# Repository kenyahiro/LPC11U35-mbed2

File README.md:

# LPC11U35-mbed2

ローカルにmbed2のビルド環境を作成したものです。

ホストはDebian/testing, コンパイラはarm-none-eabi-gcc を使います。

ターゲットはLPC11U35のみ確認しています。

mbed-cliを使ってコンパイルできることを確認したあと, exportでMakefileを生成しました。

割り込みベクタにチェックサムを埋め込むため、 スタートアップとリンカスクリプトを修正しました。
また、CRPの値を設定しています。

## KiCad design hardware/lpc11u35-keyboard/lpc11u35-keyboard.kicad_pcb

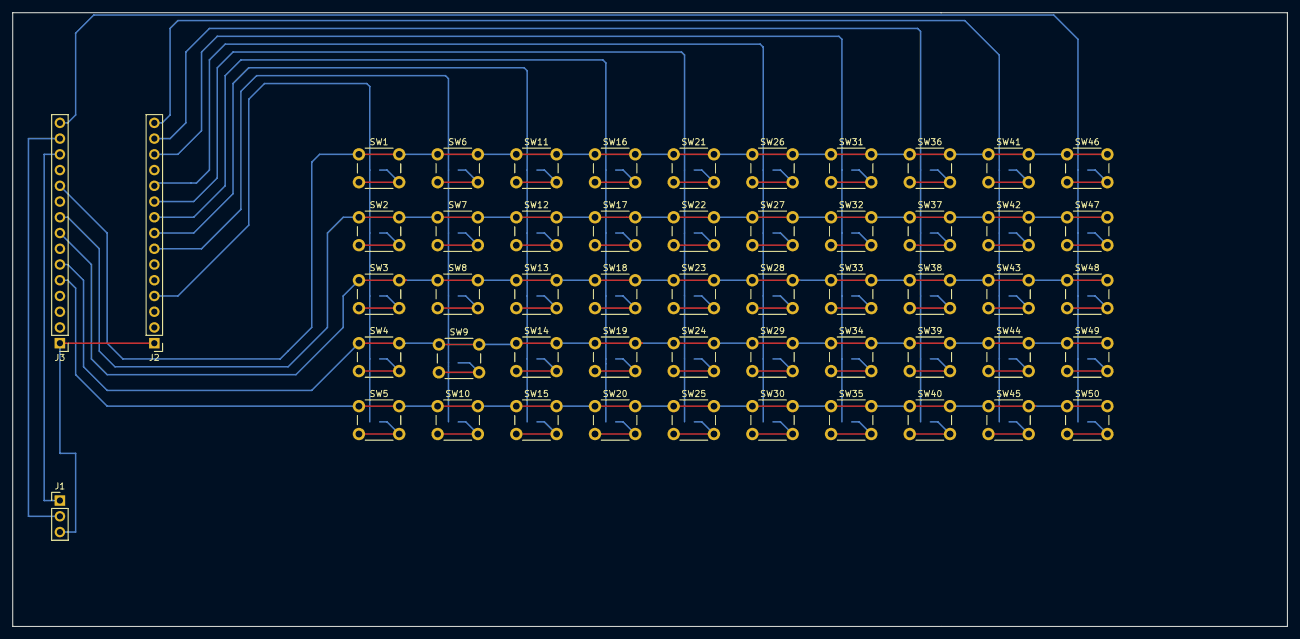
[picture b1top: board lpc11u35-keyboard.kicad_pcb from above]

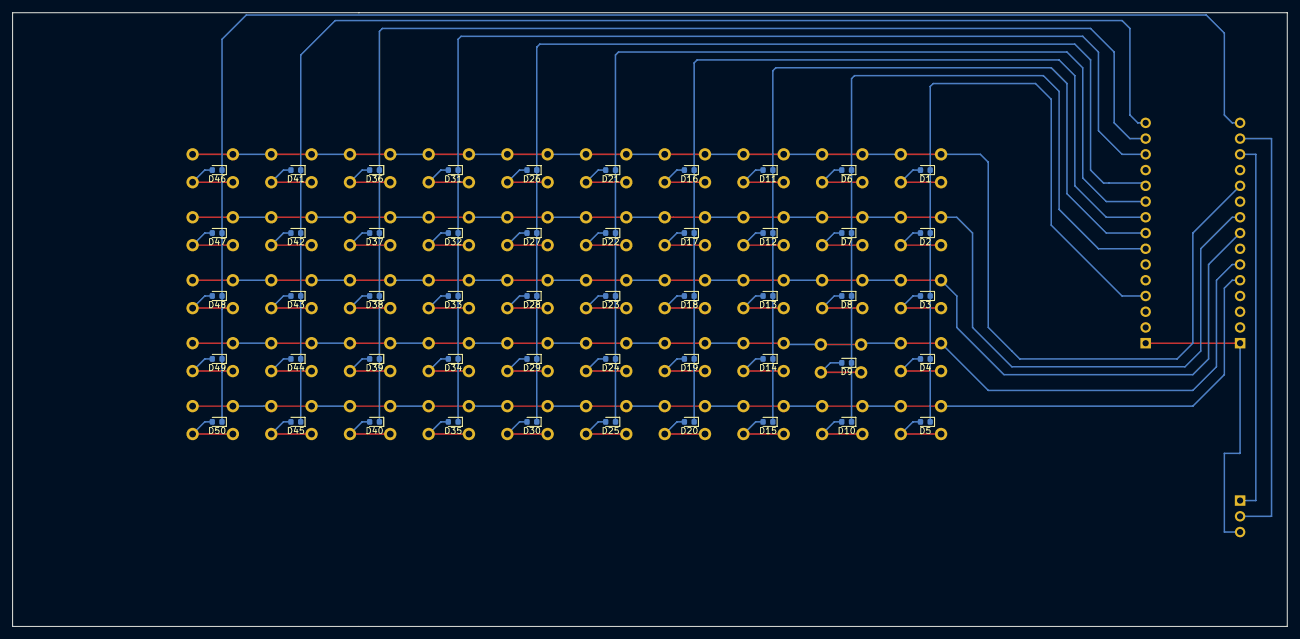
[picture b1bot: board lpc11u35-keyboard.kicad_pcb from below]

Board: 2 copper layers, 205.7 x 99.1 mm, 103 parts (50 on the bottom side), 68 nets.

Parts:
D1, D2, D3, D4, D5, D6, D7, D8, D9, D10, D11, D12, D13, D14, D15, D16, D17, D18, D19, D20, D21, D22, D23, D24, D25, D26, D27, D28, D29, D30, D31, D32, D33, D34, D35, D36, D37, D38, D39, D40, D41, D42, D43, D44, D45, D46, D47, D48, D49, D50: D_Small; D_0603_1608Metric
J1: Conn_01x03; PinHeader_1x03_P2.54mm_Vertical
J2, J3: Conn_01x15; PinHeader_1x15_P2.54mm_Vertical
SW1, SW2, SW3, SW4, SW5, SW6, SW7, SW8, SW9, SW10, SW11, SW12, SW13, SW14, SW15, SW16, SW17, SW18, SW19, SW20, SW21, SW22, SW23, SW24, SW25, SW26, SW27, SW28, SW29, SW30, SW31, SW32, SW33, SW34, SW35, SW36, SW37, SW38, SW39, SW40, SW41, SW42, SW43, SW44, SW45, SW46, SW47, SW48, SW49, SW50: SW_Push; SW_PUSH_6mm_H7.3mm

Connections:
/P0_2: J3.8, SW3.1, SW8.1, SW13.1, SW18.1, SW23.1, SW28.1, SW33.1, SW38.1, SW43.1, SW48.1
/P0_4: J3.6, SW4.1, SW9.1, SW14.1, SW19.1, SW24.1, SW29.1, SW34.1, SW39.1, SW44.1, SW49.1
/P0_5: J3.5, SW5.1, SW10.1, SW15.1, SW20.1, SW25.1, SW30.1, SW35.1, SW40.1, SW45.1, SW50.1
/P0_8: D1.1, D2.1, D3.1, D4.1, D5.1, J2.4
/P0_11: D11.1, D12.1, D13.1, D14.1, D15.1, J2.8
/P0_12: D16.1, D17.1, D18.1, D19.1, D20.1, J2.9
/P0_13: D21.1, D22.1, D23.1, D24.1, D25.1, J2.10
/P0_14: D26.1, D27.1, D28.1, D29.1, D30.1, J2.11
/P0_16: D31.1, D32.1, D33.1, D34.1, D35.1, J2.13
/P0_17: D46.1, D47.1, D48.1, D49.1, D50.1, J3.15
/P0_18: J1.2, J3.14
/P0_19: J1.1, J3.13
/P0_20: J3.9, SW2.1, SW7.1, SW12.1, SW17.1, SW22.1, SW27.1, SW32.1, SW37.1, SW42.1, SW47.1
/P0_22: D6.1, D7.1, D8.1, D9.1, D10.1, J2.7
/P0_23: D36.1, D37.1, D38.1, D39.1, D40.1, J2.14
/P1_15: D41.1, D42.1, D43.1, D44.1, D45.1, J2.15
/P1_19: J3.11, SW1.1, SW6.1, SW11.1, SW16.1, SW21.1, SW26.1, SW31.1, SW36.1, SW41.1, SW46.1
GND: J1.3, J2.1, J3.1
unnamed: D1.2, SW1.2
unnamed: D2.2, SW2.2
unnamed: D3.2, SW3.2
unnamed: D4.2, SW4.2
unnamed: D5.2, SW5.2
unnamed: D6.2, SW6.2
unnamed: D7.2, SW7.2
unnamed: D8.2, SW8.2
unnamed: D9.2, SW9.2
unnamed: D10.2, SW10.2
unnamed: D11.2, SW11.2
unnamed: D12.2, SW12.2
unnamed: D13.2, SW13.2
unnamed: D14.2, SW14.2
unnamed: D15.2, SW15.2
unnamed: D16.2, SW16.2
unnamed: D17.2, SW17.2
unnamed: D18.2, SW18.2
unnamed: D19.2, SW19.2
unnamed: D20.2, SW20.2
unnamed: D21.2, SW21.2
unnamed: D22.2, SW22.2
unnamed: D23.2, SW23.2
unnamed: D24.2, SW24.2
unnamed: D25.2, SW25.2
unnamed: D26.2, SW26.2
unnamed: D27.2, SW27.2
unnamed: D28.2, SW28.2
unnamed: D29.2, SW29.2
unnamed: D30.2, SW30.2
unnamed: D31.2, SW31.2
unnamed: D32.2, SW32.2
unnamed: D33.2, SW33.2
unnamed: D34.2, SW34.2
unnamed: D35.2, SW35.2
unnamed: D36.2, SW36.2
unnamed: D37.2, SW37.2
unnamed: D38.2, SW38.2
unnamed: D39.2, SW39.2
unnamed: D40.2, SW40.2
unnamed: D41.2, SW41.2
unnamed: D42.2, SW42.2
unnamed: D43.2, SW43.2
unnamed: D44.2, SW44.2
unnamed: D45.2, SW45.2
unnamed: D46.2, SW46.2
unnamed: D47.2, SW47.2
unnamed: D48.2, SW48.2
unnamed: D49.2, SW49.2
unnamed: D50.2, SW50.2

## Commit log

2020-12-31 mbed-cliで生成したMakefileを元にコンパイル環境を整えました。 割り込みベクタにチェックサムを埋め込むようにしました。 CRPに定数を設定しました。
2020-12-31 このリポジトリの説明を追加しました。
2021-01-11 キーボードの回路図を追加しました。
